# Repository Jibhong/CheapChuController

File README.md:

### A Controller For That Specific Slider Game

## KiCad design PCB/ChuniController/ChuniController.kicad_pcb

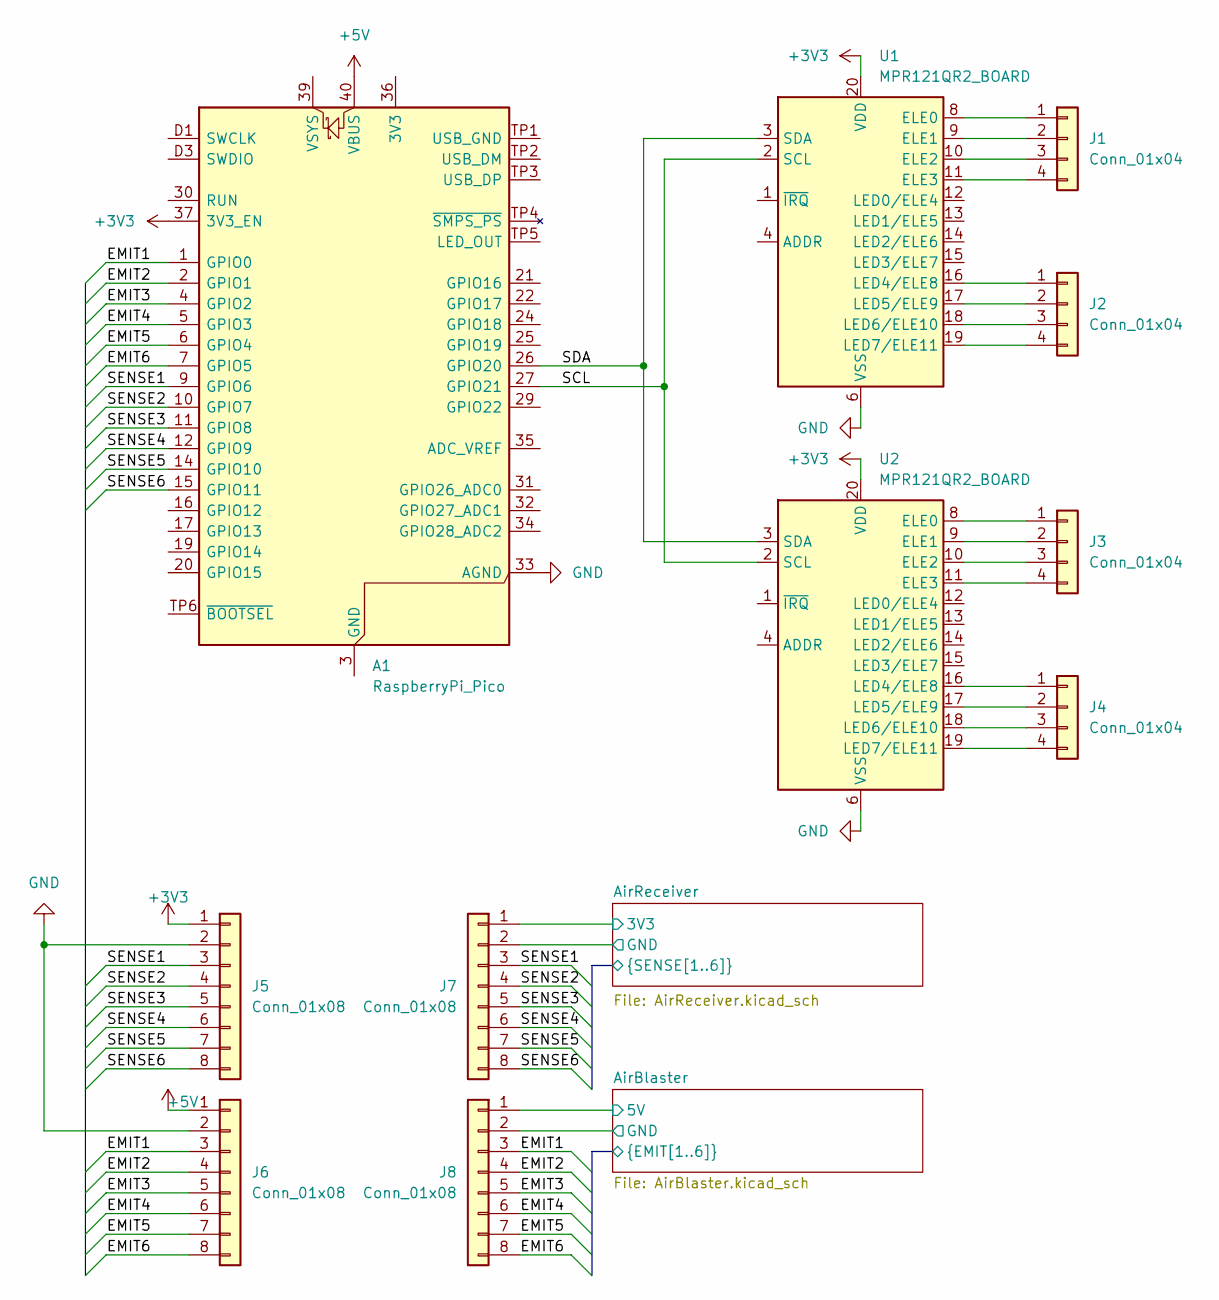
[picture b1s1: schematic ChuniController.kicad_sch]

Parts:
A1: RaspberryPi_Pico; RaspberryPi_Pico_SMD
J1, J2, J3: Conn_01x04
J4: Conn_01x04; JST_SH_SM04B-SRSS-TB_1x04-1MP_P1.00mm_Horizontal
J5, J6, J7, J8: Conn_01x08; JST_SH_SM08B-SRSS-TB_1x08-1MP_P1.00mm_Horizontal
U1, U2: MPR121QR2_BOARD; MPR121_BOARD

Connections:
+3V3: A1.37 (3V3_EN), J5.1, J7.1, U1.20 (VDD), U2.20 (VDD); also elsewhere on the board
+5V: A1.40 (VBUS), J6.1
/AirBlaster/5V: J8.1; also elsewhere on the board
/AirBlaster/EMIT1: A1.1 (GPIO0), J6.3, J8.3; also elsewhere on the board
/AirBlaster/EMIT2: A1.2 (GPIO1), J6.4, J8.4; also elsewhere on the board
/AirBlaster/EMIT3: A1.4 (GPIO2), J6.5, J8.5; also elsewhere on the board
/AirBlaster/EMIT4: A1.5 (GPIO3), J6.6, J8.6; also elsewhere on the board
/AirBlaster/EMIT5: A1.6 (GPIO4), J6.7, J8.7; also elsewhere on the board
/AirBlaster/EMIT6: A1.7 (GPIO5), J6.8, J8.8; also elsewhere on the board
/AirBlaster/GND: J8.2; also elsewhere on the board
/AirReceiver/SENSE1: A1.9 (GPIO6), J5.3, J7.3; also elsewhere on the board
/AirReceiver/SENSE2: A1.10 (GPIO7), J5.4, J7.4; also elsewhere on the board
/AirReceiver/SENSE3: A1.11 (GPIO8), J5.5, J7.5; also elsewhere on the board
/AirReceiver/SENSE4: A1.12 (GPIO9), J5.6, J7.6; also elsewhere on the board
/AirReceiver/SENSE5: A1.14 (GPIO10), J5.7, J7.7; also elsewhere on the board
/AirReceiver/SENSE6: A1.15 (GPIO11), J5.8, J7.8; also elsewhere on the board
/SCL: A1.27 (GPIO21), U1.2 (SCL), U2.2 (SCL)
/SDA: A1.26 (GPIO20), U1.3 (SDA), U2.3 (SDA)
GND: A1.33 (AGND), J5.2, J6.2, J7.2, U1.6 (VSS), U2.6 (VSS); also elsewhere on the board
unnamed: A1.3 (GND), A1.8 (GND), A1.13 (GND), A1.18 (GND), A1.23 (GND), A1.28 (GND), A1.38 (GND), A1.D2 (GND)
unnamed: J1.1, U1.8 (ELE0)
unnamed: J1.2, U1.9 (ELE1)
unnamed: J1.3, U1.10 (ELE2)
unnamed: J1.4, U1.11 (ELE3)
unnamed: J2.1, U1.16 (LED4/ELE8)
unnamed: J2.2, U1.17 (LED5/ELE9)
unnamed: J2.3, U1.18 (LED6/ELE10)
unnamed: J2.4, U1.19 (LED7/ELE11)
unnamed: J3.1, U2.8 (ELE0)
unnamed: J3.2, U2.9 (ELE1)
unnamed: J3.3, U2.10 (ELE2)
unnamed: J3.4, U2.11 (ELE3)
unnamed: J4.1, U2.16 (LED4/ELE8)
unnamed: J4.2, U2.17 (LED5/ELE9)
unnamed: J4.3, U2.18 (LED6/ELE10)
unnamed: J4.4, U2.19 (LED7/ELE11)

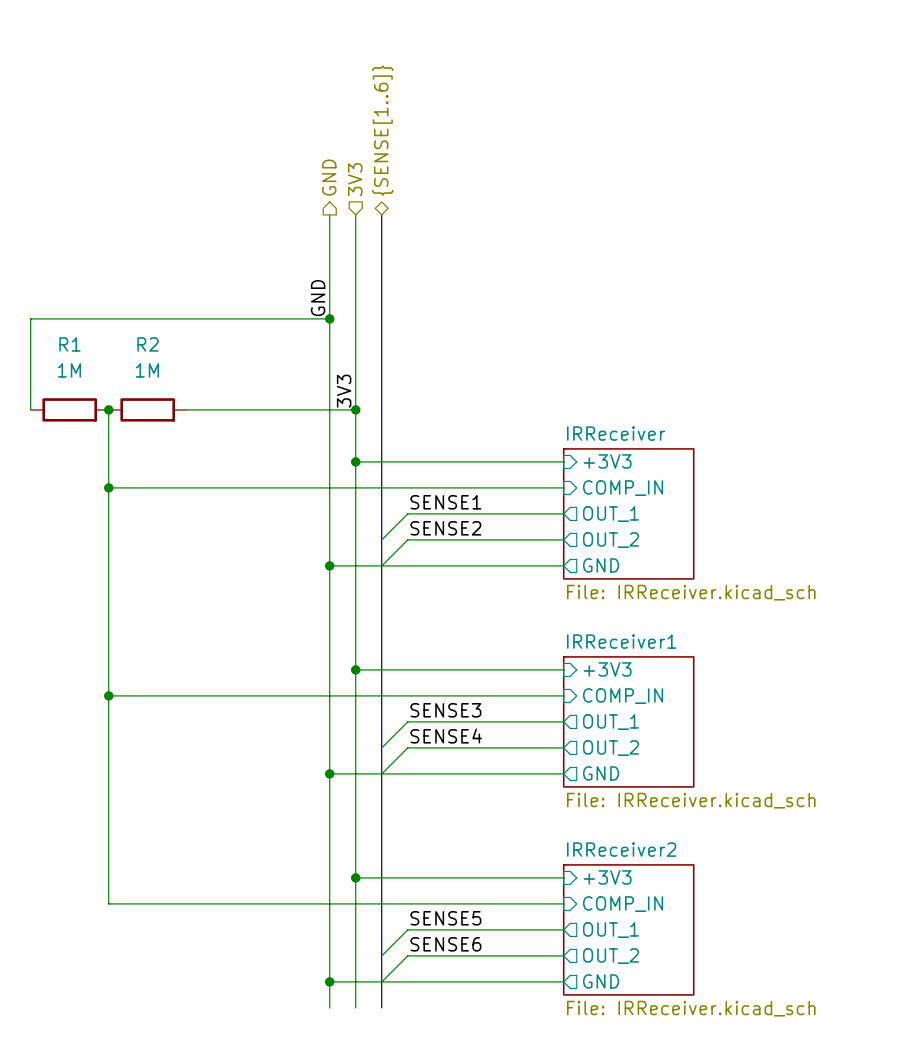
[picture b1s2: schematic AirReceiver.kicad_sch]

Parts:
R1, R2: 1M; R_0805_2012Metric_Pad1.20x1.40mm_HandSolder

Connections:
+3V3: R2.2; also elsewhere on the board
/AirReceiver/IRReceiver/COMP_IN: R1.2, R2.1; also elsewhere on the board
GND: R1.1; also elsewhere on the board

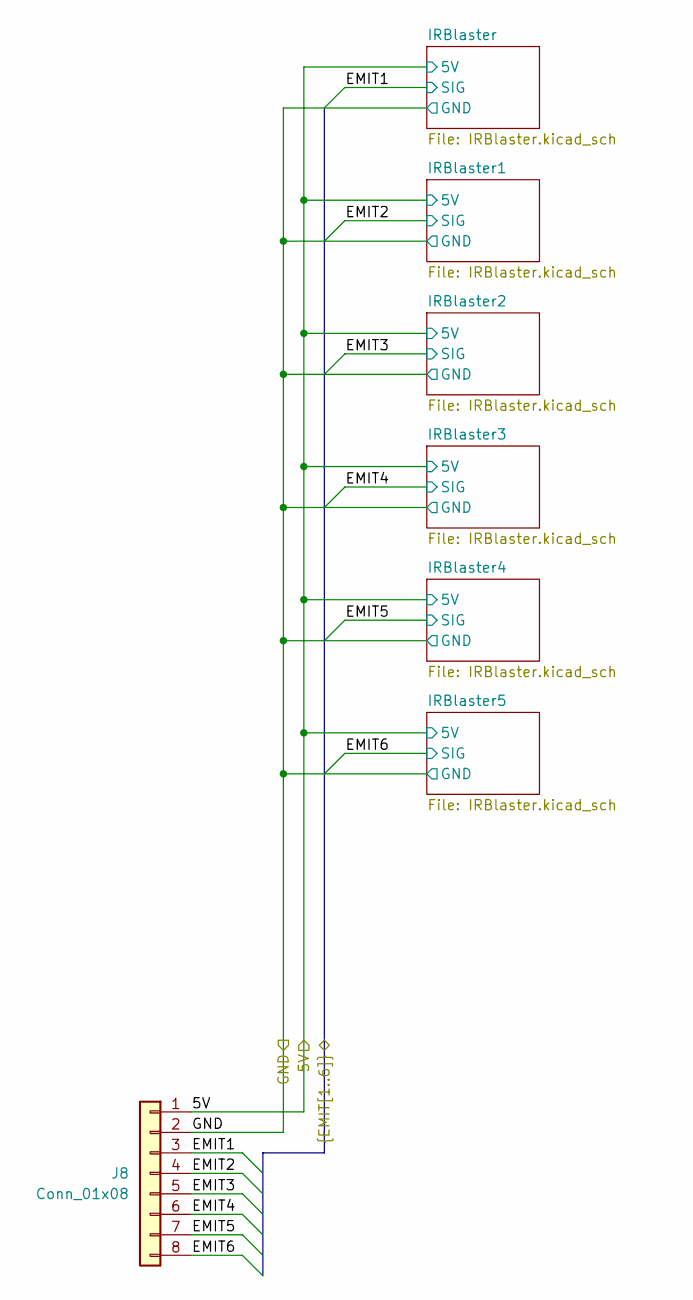
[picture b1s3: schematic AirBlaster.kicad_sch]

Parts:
J8: Conn_01x08; JST_SH_SM08B-SRSS-TB_1x08-1MP_P1.00mm_Horizontal

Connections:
/AirBlaster/5V: J8.1; also elsewhere on the board
/AirBlaster/EMIT1: J8.3; also elsewhere on the board
/AirBlaster/EMIT2: J8.4; also elsewhere on the board
/AirBlaster/EMIT3: J8.5; also elsewhere on the board
/AirBlaster/EMIT4: J8.6; also elsewhere on the board
/AirBlaster/EMIT5: J8.7; also elsewhere on the board
/AirBlaster/EMIT6: J8.8; also elsewhere on the board
/AirBlaster/GND: J8.2; also elsewhere on the board

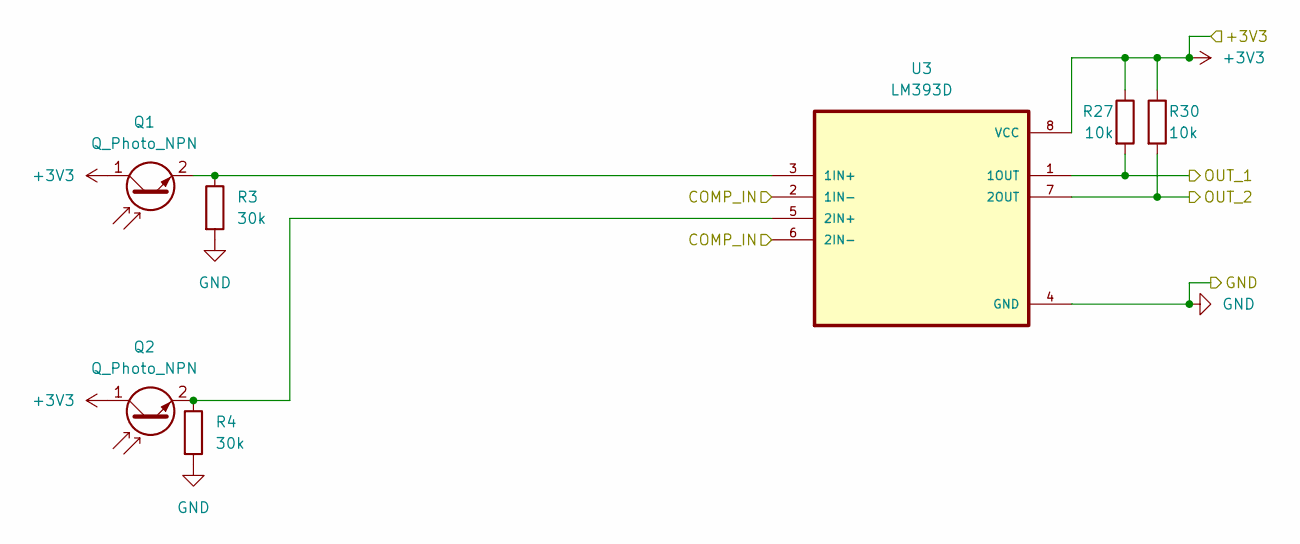
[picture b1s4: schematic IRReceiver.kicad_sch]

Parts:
Q1, Q2: Q_Photo_NPN; LED_D5.0mm
R3, R4: 30k; R_0805_2012Metric_Pad1.20x1.40mm_HandSolder
R27, R30: 10k; R_0805_2012Metric_Pad1.20x1.40mm_HandSolder
U3: LM393D; SOIC127P600X175-8N

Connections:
+3V3: Q1.1 (C), Q2.1 (C), R27.1, R30.1, U3.8 (VCC); also elsewhere on the board
/AirReceiver/IRReceiver/COMP_IN: U3.2 (1IN-), U3.6 (2IN-); also elsewhere on the board
/AirReceiver/SENSE1: R27.2, U3.1 (1OUT); also elsewhere on the board
/AirReceiver/SENSE2: R30.2, U3.7 (2OUT); also elsewhere on the board
GND: R3.2, R4.2, U3.4 (GND); also elsewhere on the board
unnamed: Q1.2 (E), R3.1, U3.3 (1IN+)
unnamed: Q2.2 (E), R4.1, U3.5 (2IN+)

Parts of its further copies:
Q3, Q4, Q5, Q6: Q_Photo_NPN; LED_D5.0mm
R5, R6, R7, R8: 30k; R_0805_2012Metric_Pad1.20x1.40mm_HandSolder
R28, R29, R31, R32: 10k; R_0805_2012Metric_Pad1.20x1.40mm_HandSolder
U4, U5: LM393D; SOIC127P600X175-8N

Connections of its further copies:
+3V3: Q3.1 (C), Q4.1 (C), Q5.1 (C), Q6.1 (C), R28.1, R29.1, R31.1, R32.1, U4.8 (VCC), U5.8 (VCC); also elsewhere on the board
/AirReceiver/IRReceiver/COMP_IN: U4.2 (1IN-), U4.6 (2IN-), U5.2 (1IN-), U5.6 (2IN-); also elsewhere on the board
/AirReceiver/SENSE3: R28.2, U4.1 (1OUT); also elsewhere on the board
/AirReceiver/SENSE4: R31.2, U4.7 (2OUT); also elsewhere on the board
/AirReceiver/SENSE5: R29.2, U5.1 (1OUT); also elsewhere on the board
/AirReceiver/SENSE6: R32.2, U5.7 (2OUT); also elsewhere on the board
GND: R5.2, R6.2, R7.2, R8.2, U4.4 (GND), U5.4 (GND); also elsewhere on the board
unnamed: Q3.2 (E), R5.1, U4.3 (1IN+)
unnamed: Q4.2 (E), R6.1, U4.5 (2IN+)
unnamed: Q5.2 (E), R7.1, U5.3 (1IN+)
unnamed: Q6.2 (E), R8.1, U5.5 (2IN+)

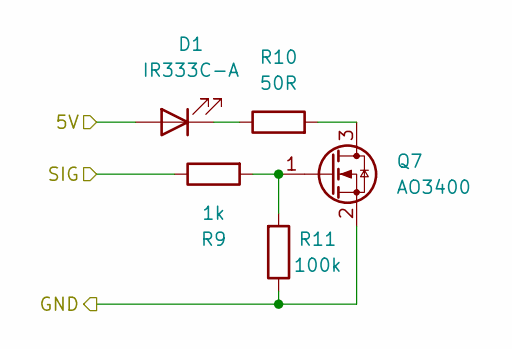
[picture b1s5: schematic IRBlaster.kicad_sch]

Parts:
D1: IR333C-A; LED_D5.0mm
Q7: AO3400; SOT-23
R9: 1k; R_0805_2012Metric_Pad1.20x1.40mm_HandSolder
R10: 50R; R_0805_2012Metric_Pad1.20x1.40mm_HandSolder
R11: 100k; R_0805_2012Metric_Pad1.20x1.40mm_HandSolder

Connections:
/AirBlaster/5V: D1.2 (A); also elsewhere on the board
/AirBlaster/EMIT1: R9.1; also elsewhere on the board
/AirBlaster/GND: Q7.2 (S), R11.1; also elsewhere on the board
unnamed: D1.1 (K), R10.1
unnamed: Q7.3 (D), R10.2
unnamed: Q7.1 (G), R9.2, R11.2

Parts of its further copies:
D2, D3, D4, D5, D6: IR333C-A; LED_D5.0mm
Q8, Q9, Q10, Q11, Q12: AO3400; SOT-23
R12, R15, R18, R21, R24: 1k; R_0805_2012Metric_Pad1.20x1.40mm_HandSolder
R13, R16, R19, R22, R25: 50R; R_0805_2012Metric_Pad1.20x1.40mm_HandSolder
R14, R17, R20, R23, R26: 100k; R_0805_2012Metric_Pad1.20x1.40mm_HandSolder

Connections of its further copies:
/AirBlaster/5V: D2.2 (A), D3.2 (A), D4.2 (A), D5.2 (A), D6.2 (A); also elsewhere on the board
/AirBlaster/EMIT2: R12.1; also elsewhere on the board
/AirBlaster/EMIT3: R15.1; also elsewhere on the board
/AirBlaster/EMIT4: R18.1; also elsewhere on the board
/AirBlaster/EMIT5: R21.1; also elsewhere on the board
/AirBlaster/EMIT6: R24.1; also elsewhere on the board
/AirBlaster/GND: Q8.2 (S), Q9.2 (S), Q10.2 (S), Q11.2 (S), Q12.2 (S), R14.1, R17.1, R20.1, R23.1, R26.1; also elsewhere on the board
unnamed: D2.1 (K), R13.1
unnamed: D3.1 (K), R16.1
unnamed: D4.1 (K), R19.1
unnamed: D5.1 (K), R22.1
unnamed: D6.1 (K), R25.1
unnamed: Q8.3 (D), R13.2
unnamed: Q8.1 (G), R12.2, R14.2
unnamed: Q9.3 (D), R16.2
unnamed: Q9.1 (G), R15.2, R17.2
unnamed: Q10.3 (D), R19.2
unnamed: Q10.1 (G), R18.2, R20.2
unnamed: Q11.3 (D), R22.2
unnamed: Q11.1 (G), R21.2, R23.2
unnamed: Q12.3 (D), R25.2
unnamed: Q12.1 (G), R24.2, R26.2

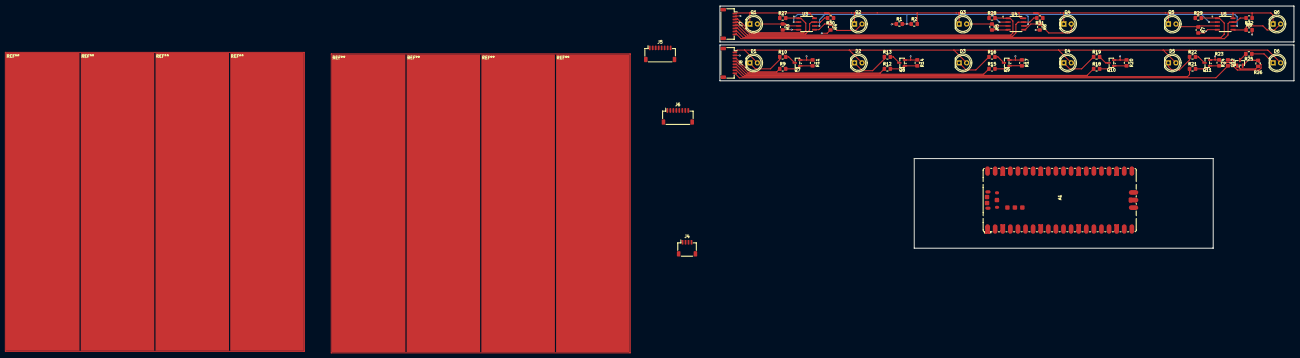
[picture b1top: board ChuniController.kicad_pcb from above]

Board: 2 copper layers, 192.0 x 81.0 mm, 59 parts (0 on the bottom side), 43 nets.
